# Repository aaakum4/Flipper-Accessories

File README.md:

# Flipper-Accessories
Now that I have made a custom Flipper, I use create some accessories for it to go with.

A custom expansion board for the Flipper Zero that adds WiFi capability and a high-power IR blaster, designed with safety, flexibility, and future expansion in mind.

This project was designed specifically for my custom Flipper Zero build, which can be found here:
https://github.com/aaakum4/Sorta-Flipper-Zero

While the designs and files are shared openly, they should not be blindly copied or connected to a stock Flipper Zero without understanding the electrical implications. Component choices, power rails, and protection methods were selected with my particular setup and use case in mind.
If you choose to reuse or adapt any part of this project, please make sure it will work with whatever device you are using.

## Overview
This project combines two main subsystems:
- A WiFi board built around the ESP32-S2-WROVER-N4R2 for networking and future firmware experiments
- A 960 nm IR blaster designed for high-power pulsed output while keeping the Flipper electrically isolated

The goal wasn’t just to make something that works, but to make something that’s understandable, modifiable, and safe to plug into a Flipper.

## The WiFi Board
The WiFi side uses the ESP32-S2-WROVER-N4R2, which offered more than enough performance without being unnecessarily complex. Since this board is meant to be reused and extended, several design choices were made with development and debugging in mind:
- Spare GPIO pins left uncommitted for future features
- JTAG and UART exposed for debugging and flashing
- Dedicated BOOT and RESET buttons to avoid relying on awkward software-only recovery

Rather than pushing for maximum performance, the focus here was reliability, ease of development, and not boxing the design into a single use case.

## IR Blaster
The IR blaster uses seven 960 nm IR LEDs, arranged as three series pairs plus one standalone LED, which allowed higher optical output while still working comfortably from a 5 V rail.

A logic-level MOSFET is used for switching instead of a transistor, keeping all high current paths away from the Flipper’s GPIO pins and allowing clean, efficient pulsed operation. The circuit is intended for modulated IR (rather than continuous drive), which makes higher peak currents practical without excessive heat.

This part of the design involved a lot of trade-offs around current, voltage, and safety, and ended up being more conceptually challenging than the WiFi board despite using fewer components.

## Safety & Protection
A core design requirement was ensuring that the Flipper Zero is not put at risk, even in the event of a fault or design mistake. To that end:
- GPIO pins are only ever used as logic-level control signals
- High-current loads are fully isolated using switching components
- Current is limited where appropriate
- No direct power paths exist that could back-feed into the Flipper

The aim was to make the board something you can plug in without constantly worrying about damaging the host device.

## Making the PCB
Here is the final Wifi PCB:

Here is the final IR Blaster PCB:

## BOM
For those interested in the part's I am using, here is the Bill of Materials. It doesnt include the MCU (since it was out of stock when I last check on JLCPCB) and the IR LED's, but any 940nm or 960nm IR LED will do as long as it is 5mm.

## Final Note
Since this is a Flipper project, I feel like I must say that these devices shouldn't be use for any illgeal or unethical activities.

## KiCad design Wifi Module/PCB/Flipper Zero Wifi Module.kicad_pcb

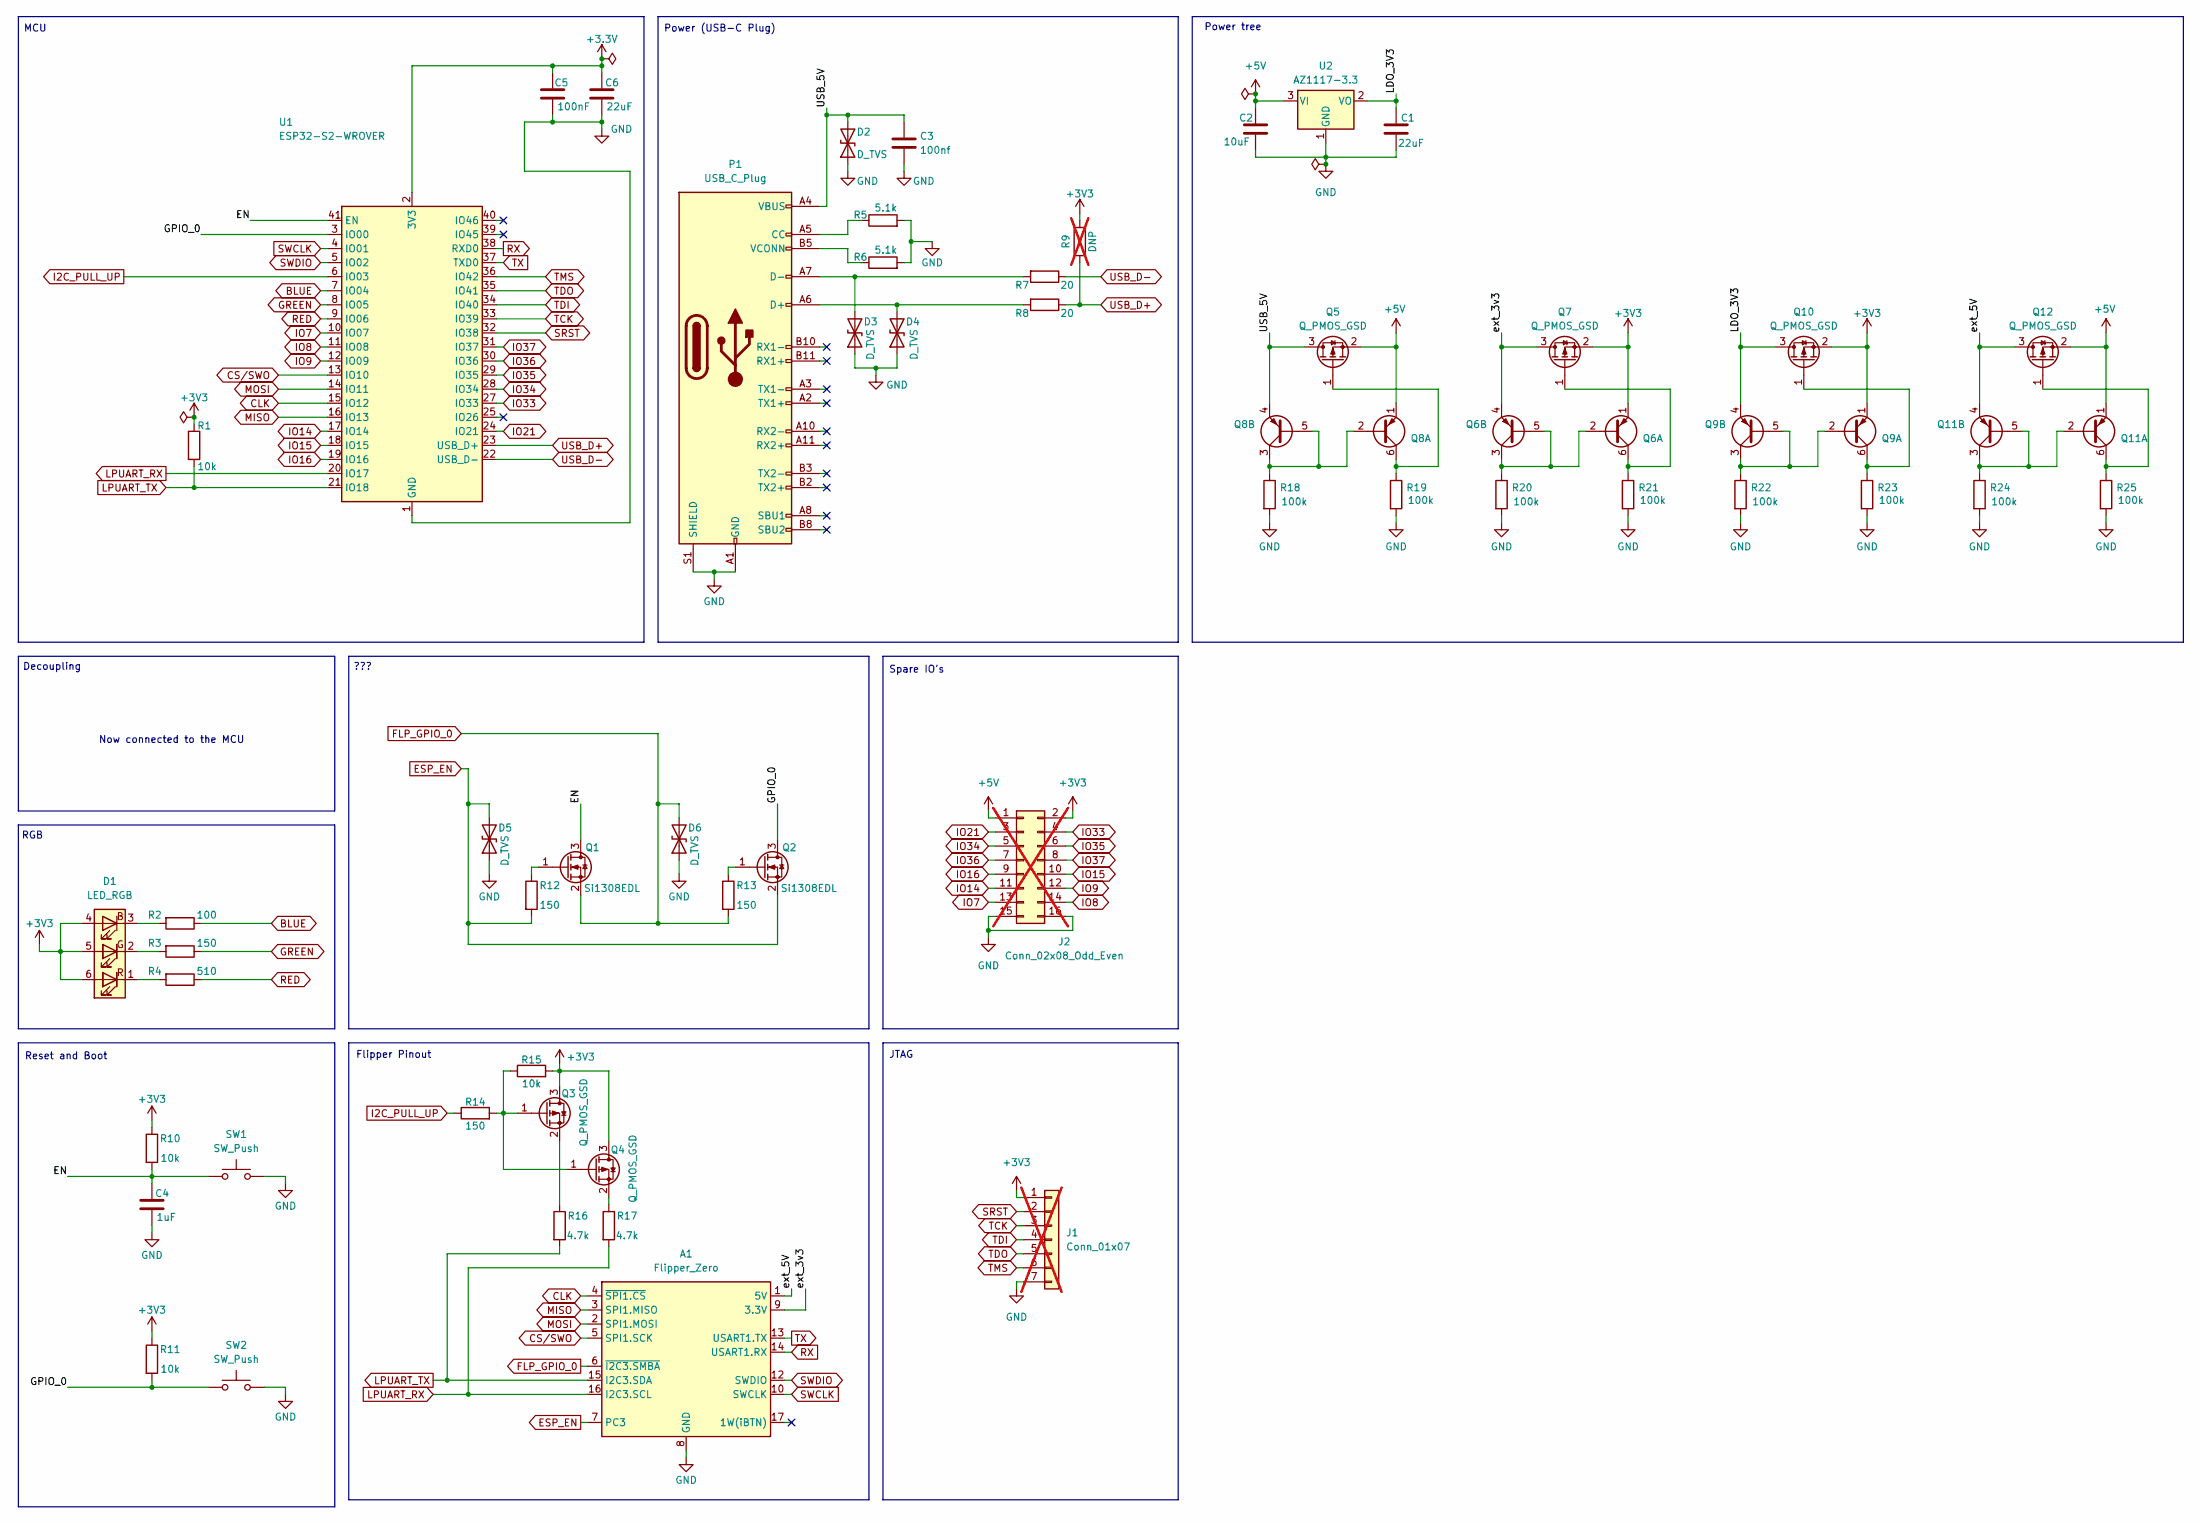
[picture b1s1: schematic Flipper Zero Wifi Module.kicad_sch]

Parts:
A1: Flipper_Zero; Flipper_Zero_Angled
C1, C6: 22uF; C_0603_1608Metric
C2: 10uF; C_0603_1608Metric
C3: 100nf; C_0603_1608Metric
C4: 1uF; C_0603_1608Metric
C5: 100nF; C_0603_1608Metric
D1: LED_RGB; LED_Avago_PLCC6_3x2.8mm
D2, D3, D4, D5, D6: D_TVS; D_0201_0603Metric
J1: Conn_01x07; PinHeader_1x07_P2.54mm_Vertical; not fitted
J2: Conn_02x08_Odd_Even; PinHeader_2x08_P2.54mm_Vertical; not fitted
P1: USB_C_Plug; USB_C_Receptacle_HRO_TYPE-C-31-M-12
Q1, Q2: Si1308EDL; SOT-323_SC-70
Q3, Q4, Q5, Q7, Q10, Q12: Q_PMOS_GSD; SOT-23
Q6, Q8, Q9, Q11: Q_Dual_PNP_PNP_E1B1C2E2B2C1; SOT-363_SC-70-6
R1, R10, R11, R15: 10k; R_0603_1608Metric
R2: 100; R_0603_1608Metric
R3, R12, R13, R14: 150; R_0603_1608Metric
R4: 510; R_0603_1608Metric
R5, R6: 5.1k; R_0603_1608Metric
R7, R8: 20; R_0603_1608Metric
R9: DNP; R_0603_1608Metric; not fitted
R16, R17: 4.7k; R_0603_1608Metric
R18, R19, R20, R21, R22, R23, R24, R25: 100k; R_0603_1608Metric
SW1, SW2: SW_Push; SW_PUSH_6mm
U1: ESP32-S2-WROVER
U2: AZ1117-3.3; SOT-223

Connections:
+3.3V: C5.1, C6.1, U1.2 (3V3)
+3V3: D1.4 (BA), D1.5 (GA), D1.6 (RA), J1.1, J2.2, Q3.3 (D), Q4.3 (D), Q6.1 (E1), Q7.2 (S), Q9.1 (E1), Q10.2 (S), R1.1, R9.1, R10.1, R11.1, R15.2
+5V: C2.1, J2.1, Q5.2 (S), Q8.1 (E1), Q11.1 (E1), Q12.2 (S), U2.3 (VI)
/EN: C4.1, Q1.3 (D), R10.2, SW1.1, U1.41 (EN)
/GPIO_0: Q2.3 (D), R11.2, SW2.1, U1.3 (IO00)
/LDO_3V3: C1.1, Q9.4 (E2), Q10.3 (D), U2.2 (VO)
/USB_5V: C3.1, D2.2 (A2), P1.A4 (VBUS), P1.A9 (VBUS), P1.B4 (VBUS), P1.B9 (VBUS), Q5.3 (D), Q8.4 (E2)
/ext_3v3: A1.9 (3.3V), Q6.4 (E2), Q7.3 (D)
/ext_5V: A1.1 (5V), Q11.4 (E2), Q12.3 (D)
BLUE: R2.1, U1.7 (IO04)
CLK: A1.4 (~SPI1.CS), U1.15 (IO12)
CS/SWO: A1.5 (SPI1.SCK), U1.13 (IO10)
ESP_EN: A1.7 (PC3), D5.2 (A2), Q2.2 (S), R12.2
FLP_GPIO_0: A1.6 (~I2C3.SMBA), D6.2 (A2), Q1.2 (S), R13.2
GND: A1.8 (GND), A1.11 (GND), A1.18 (GND), C1.2, C2.2, C3.2, C4.2, C5.2, C6.2, D2.1 (A1), D3.1 (A1), D4.1 (A1), D5.1 (A1), D6.1 (A1), J1.7, J2.15, J2.16, P1.A1 (GND), P1.A12 (GND), P1.B1 (GND), P1.B12 (GND), P1.S1 (SHIELD), R5.2, R6.2, R18.2, R19.2, R20.2, R21.2, R22.2, R23.2, R24.2, R25.2, SW1.2, SW2.2, U1.1 (GND), U1.26 (GND), U1.42 (GND), U1.43 (GND), U2.1 (GND)
GREEN: R3.1, U1.8 (IO05)
I2C_PULL_UP: R14.1, U1.6 (IO03)
IO7: J2.13, U1.10 (IO07)
IO8: J2.14, U1.11 (IO08)
IO9: J2.12, U1.12 (IO09)
IO14: J2.11, U1.17 (IO14)
IO15: J2.10, U1.18 (IO15)
IO16: J2.9, U1.19 (IO16)
IO21: J2.3, U1.24 (IO21)
IO33: J2.4, U1.27 (IO33)
IO34: J2.5, U1.28 (IO34)
IO35: J2.6, U1.29 (IO35)
IO36: J2.7, U1.30 (IO36)
IO37: J2.8, U1.31 (IO37)
LPUART_RX: A1.16 (I2C3.SCL), R17.2, U1.20 (IO17)
LPUART_TX: A1.15 (I2C3.SDA), R1.2, R16.2, U1.21 (IO18)
MISO: A1.3 (SPI1.MISO), U1.16 (IO13)
MOSI: A1.2 (SPI1.MOSI), U1.14 (IO11)
unnamed: D1.3 (BK), R2.2
unnamed: D1.2 (GK), R3.2
unnamed: D1.1 (RK), R4.2
unnamed: P1.A5 (CC), R5.1
unnamed: P1.B5 (VCONN), R6.1
unnamed: Q1.1 (G), R12.1
unnamed: Q2.1 (G), R13.1
unnamed: Q3.1 (G), Q4.1 (G), R14.2, R15.1
unnamed: Q3.2 (S), R16.1
unnamed: Q4.2 (S), R17.1
unnamed: Q5.1 (G), Q8.6 (C1), R19.1
unnamed: Q6.2 (B1), Q6.3 (C2), Q6.5 (B2), R20.1
unnamed: Q6.6 (C1), Q7.1 (G), R21.1
unnamed: Q8.2 (B1), Q8.3 (C2), Q8.5 (B2), R18.1
unnamed: Q9.2 (B1), Q9.3 (C2), Q9.5 (B2), R22.1
unnamed: Q9.6 (C1), Q10.1 (G), R23.1
unnamed: Q11.2 (B1), Q11.3 (C2), Q11.5 (B2), R24.1
unnamed: Q11.6 (C1), Q12.1 (G), R25.1
RED: R4.1, U1.9 (IO06)
RX: A1.14 (USART1.RX), U1.38 (RXD0)
SRST: J1.2, U1.32 (IO38)
SWCLK: A1.10 (SWCLK), U1.4 (IO01)
SWDIO: A1.12 (SWDIO), U1.5 (IO02)
TCK: J1.3, U1.33 (IO39)
TDI: J1.4, U1.34 (IO40)
TDO: J1.5, U1.35 (IO41)
TMS: J1.6, U1.36 (IO42)
TX: A1.13 (USART1.TX), U1.37 (TXD0)

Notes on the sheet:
Flipper Pinout
Reset and Boot
Now connected to the MCU
???
Spare IO's
MCU
Power (USB-C Plug)
JTAG
Decoupling
RGB
Power tree

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
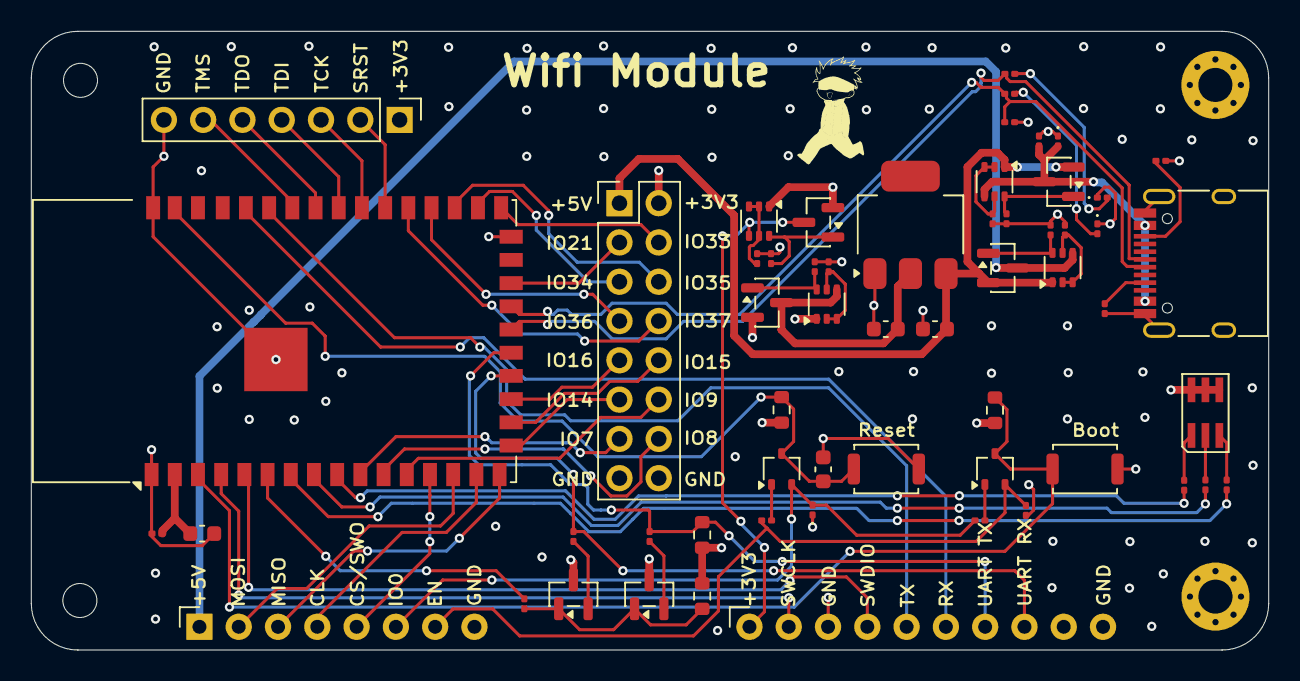
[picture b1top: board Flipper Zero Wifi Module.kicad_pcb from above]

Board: 4 copper layers, 80.0 x 40.0 mm, 57 parts (0 on the bottom side), 65 nets.

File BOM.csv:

Comment,Designator,Footprint,JLCPCB Part #
100k,"R18,R19,R20,R21,R22,R23,R24,R25",0201,C270364
USB_C_Plug,P1,SMD,C165948
510,R4,0201,C18164337
100nf,"C3,C5",0201,C76934
AZ1117-3.3,U2,SOT-223,C7432020
4.7k,"R16,R17",0201,C270346
5.1k,"R5,R6",0201,C270344
Si1308EDL,"Q1,Q2",SOT-323,C7603347
Q_Dual_PNP_PNP_E1B1C2E2B2C1,"Q11,Q6,Q8,Q9",SOT-363,C154783
150,"R12,R13,R14,R3",0201,C7467287
D_TVS,"D2,D3,D4,D5,D6",0201,C521888
100,R2,0201,C304499
SW_Push,"SW1,SW2","SMD,3.9x2.9mm",C202388
22uF,"C1,C6",0603,C59461
1uF,C4,0603,C15849
LED_RGB,D1,SMD5050-8P,C6795892
10k,"R1,R10,R11,R15",0603,C25804
20,"R7,R8",0201,C320753
Q_PMOS_GSD,"Q10,Q12,Q3,Q4,Q5,Q7",SOT-23-3,C968645
10uF,C2,0603,C19702
,,,
,,,
,,,
Comment,Designator,Footprint,JLCPCB Part #
5.6,"R2,R3,R4",1206,C137246
Q_NMOS_GSD(RDsON),Q5,SOT-23,C78755
100k,R5,603,C25803
12,R1,1206,C17913
470,R7,603,C23179

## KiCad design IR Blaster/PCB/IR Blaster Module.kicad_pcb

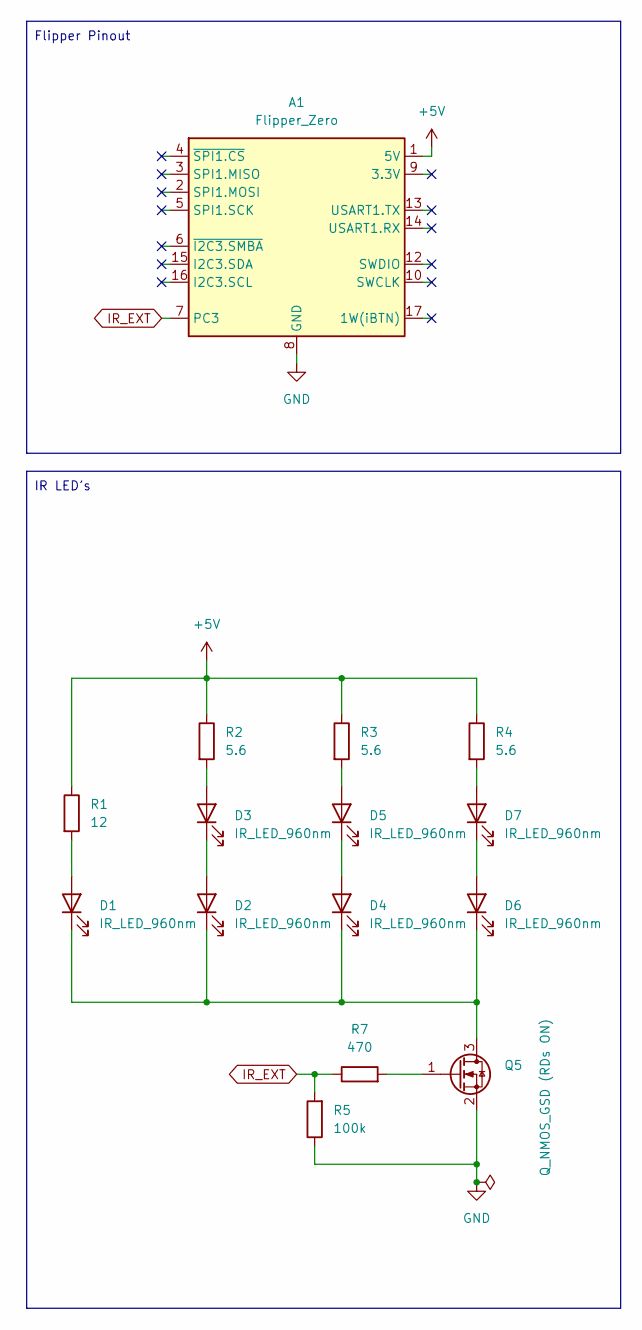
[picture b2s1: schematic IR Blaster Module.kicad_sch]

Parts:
A1: Flipper_Zero; Flipper_Zero_Angled
D1, D2, D3, D4, D5, D6, D7: IR_LED_960nm; LED_D5.0mm
Q5: Q_NMOS_GSD (RDs ON); SOT-23
R1: 12; R_1206_3216Metric
R2, R3, R4: 5.6; R_1206_3216Metric
R5: 100k; R_0603_1608Metric
R7: 470; R_0603_1608Metric

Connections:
+5V: A1.1 (5V), R1.1, R2.1, R3.1, R4.1
GND: A1.8 (GND), A1.11 (GND), A1.18 (GND), Q5.2 (S), R5.1
IR_EXT: A1.7 (PC3), R5.2, R7.1
unnamed: D1.2 (A), R1.2
unnamed: D1.1 (K), D2.1 (K), D4.1 (K), D6.1 (K), Q5.3 (D)
unnamed: D2.2 (A), D3.1 (K)
unnamed: D3.2 (A), R2.2
unnamed: D4.2 (A), D5.1 (K)
unnamed: D5.2 (A), R3.2
unnamed: D6.2 (A), D7.1 (K)
unnamed: D7.2 (A), R4.2
unnamed: Q5.1 (G), R7.2

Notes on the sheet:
Flipper Pinout
IR LED's

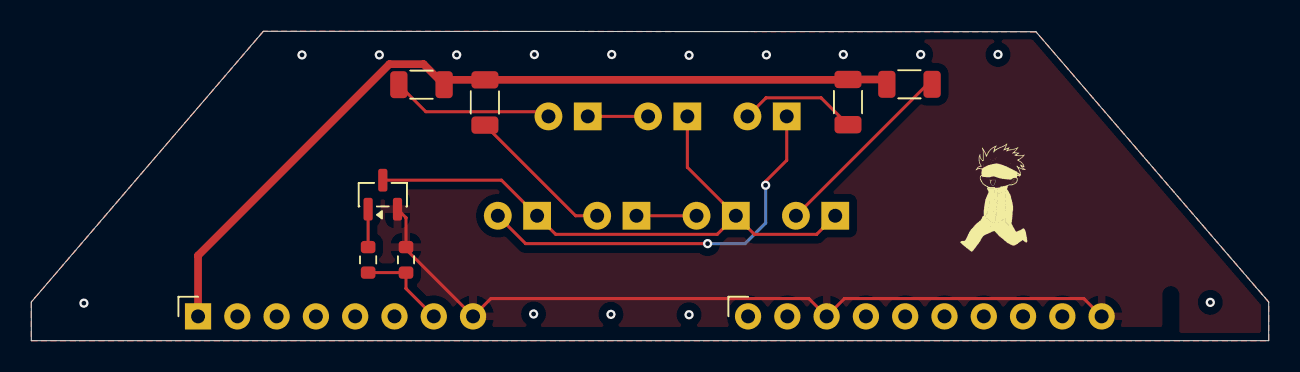
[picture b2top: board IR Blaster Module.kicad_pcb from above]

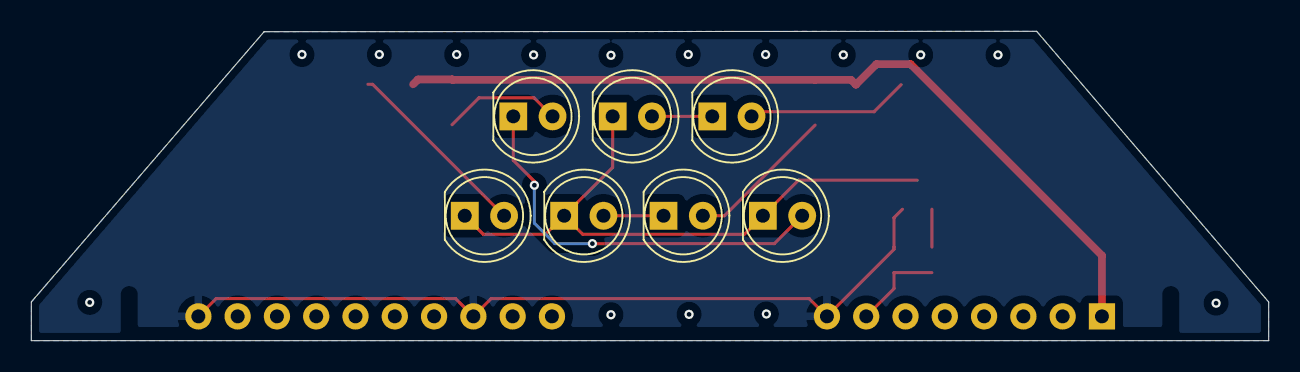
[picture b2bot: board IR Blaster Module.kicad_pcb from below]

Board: 2 copper layers, 80.0 x 20.0 mm, 15 parts (7 on the bottom side), 12 nets.

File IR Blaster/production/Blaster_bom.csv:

Designator,Footprint,Quantity,Value,LCSC Part #
A1,Flipper_Zero_Angled,1,Flipper_Zero,
"D1, D2, D3, D4, D5, D6, D7",LED_D5.0mm,7,IR_LED_960nm,
Q5,SOT-23,1,Q_NMOS_GSD (RDs ON),
R1,1206,1,12,
"R2, R3, R4",1206,3,5.6,
R5,0603,1,100k,
R7,0603,1,470,

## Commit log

2026-01-30 Add GNU GPL v3 license file
    Added the GNU General Public License version 3 to the project.
2026-01-30 Enhance README with project overview and details
    Expanded the README to include detailed descriptions of the WiFi board, IR blaster, and safety features.
2026-01-30 Enhance README with project information and cautions
    Added project details and usage warnings for the custom Flipper Zero build.
2026-01-30 Added schematic files for the IR Blaster and Wifi Module
2026-02-02 Update README with final PCB images
    Added images of final Wifi and IR Blaster PCBs.
2026-02-02 Added PCB Files and Production Files
2026-02-03 Update README with BOM and final note
    Added BOM section and final note to README.
